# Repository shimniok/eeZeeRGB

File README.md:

eeZeeRGB is a breadboard breakout board for the WS2812B smart RGB LED.

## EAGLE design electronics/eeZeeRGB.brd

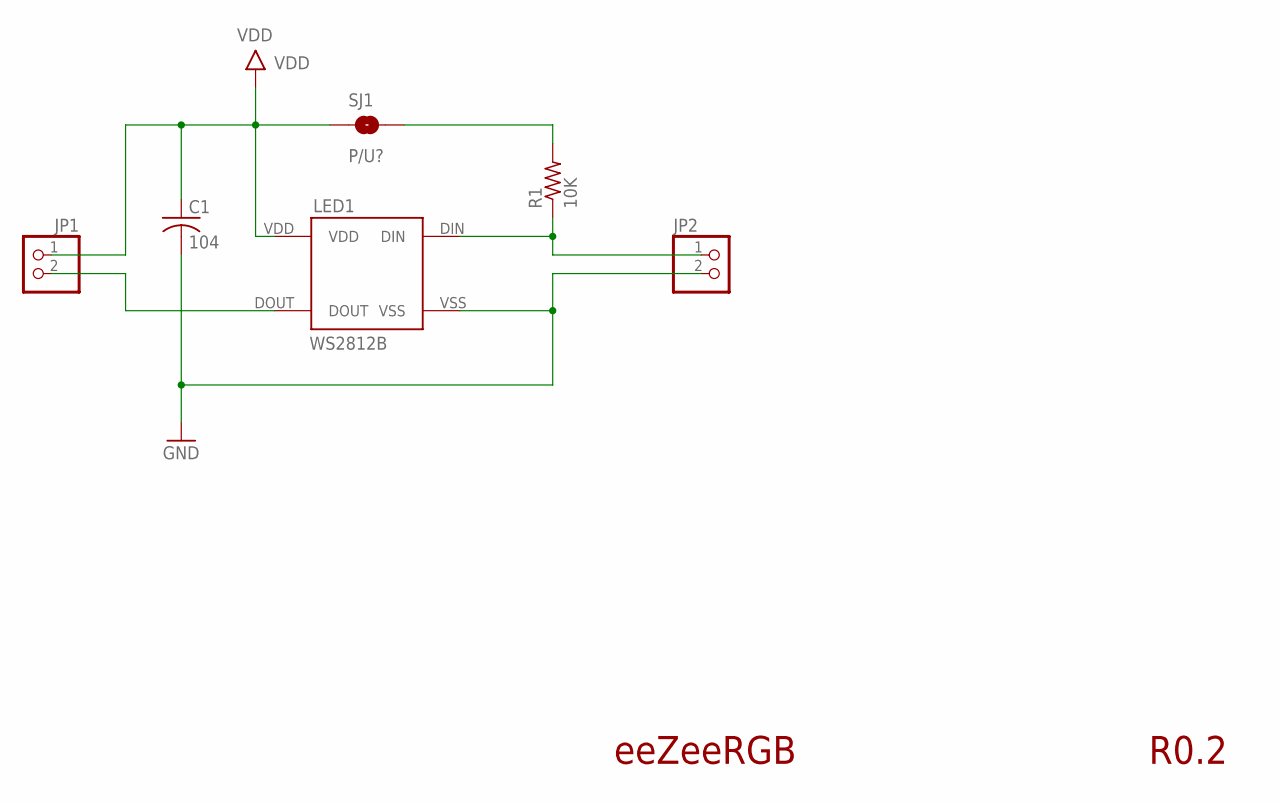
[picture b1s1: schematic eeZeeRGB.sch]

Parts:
C1: 104; C0603
JP1, JP2: PINHD-1X02_2.54-S; 1X02-S
LED1: WS2812B
R1: 10K; R0603
SJ1: P/U?; SJ_2S

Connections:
DIN: JP2.1, LED1.DIN, R1.1
DOUT: JP1.2, LED1.DOUT
GND: C1.2, JP2.2, LED1.VSS
unnamed: R1.2, SJ1.2
VDD: C1.1, JP1.1, LED1.VDD, SJ1.1

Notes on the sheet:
eeZeeRGB
R0.2

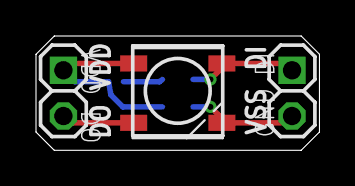
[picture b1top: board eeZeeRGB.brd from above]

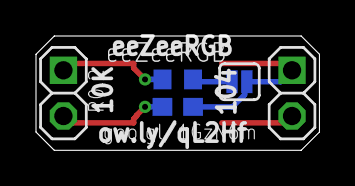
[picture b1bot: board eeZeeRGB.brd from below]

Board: 2 copper layers, 15.7 x 6.3 mm, 6 parts (5 on the bottom side), 5 nets.

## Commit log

2013-11-12 Initial version of breadboard WS2812B
2013-11-25 Moved electronics into separate folder, created firmware example
2013-11-25 Revised RGB firmware to maintain approximately constant power
2013-11-25 Removed definitions file, converted to my own ino code, updated license and comments/documentation
2014-05-12 Fixed include for missing (unnecessary) header
2014-09-30 Added light_WS2812 library/examples for AVR.
2014-09-30 Minor mods to Arduino firmware. Updated README with info about new AVR examples with light_WS2812 library.
2014-09-30 Added gerbers for main board and test jig. Added test jig sch and brd.
2014-09-30 Added project documentation box thingy.
2014-09-30 Added new example to cycle through colors smoothly, similar to my Arduino demo.
2015-05-04 updated firmware readme
2015-05-04 Revised licenses
2015-05-04 added firmware license
2015-05-04 removed root license
2015-11-12 added solder jumper to disable 10k pullup, moved passives layout, minor silk changes, changed silk for ws2812b
2015-11-12 added documentation (migrated from google code)
2015-11-12 renamed documentation to readme
2015-11-12 silk fixes for passives, shrunk board width, fixed version silk, moved pin labels after mirroring pin headers
2015-11-12 renamed firmware to examples
2015-11-12 updated gerbers, zip
2015-11-12 added assy images for documentation
2015-11-12 updated readme with soldering pics and additional info
2015-11-12 added isporopyl image; updated docs with link to purchase and fixed assembly image links
2015-11-12 Added quickstart, redid header format, reorganized code quick starts, additional minor tweaks
2015-11-12 Increased width to accommodate minimum width rule from OSHpark
2017-06-05 updated readme example links

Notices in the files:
parts and their libraries:
SparkFun-Retired: Licensing:Creative Commons ShareAlike 4.0 International - https://creativecommons.org/licenses/by-sa/4.0
